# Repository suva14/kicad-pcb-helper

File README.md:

# kicad-pcb-helper

My notebook of lessons from designing KiCad boards with [Claude Code](https://claude.com/claude-code),
kept as a skill so the next project starts where the last one ended. It works alongside
[kicad-happy](https://github.com/aklofas/kicad-happy), which does the heavy design analysis; this
plugin adds what the hand rework of one real board taught: how a human places and routes, the check to
run after every save, the review before ordering, and JLCPCB placement files that land on the right pads.

## Origin

Everything started with **[kicad-happy](https://github.com/aklofas/kicad-happy)** by aklofas, a Claude
Code plugin that parses KiCad schematics and layouts, runs EMC pre-compliance, checks gerbers and
prepares boards for fabrication. It reviewed the design of a small battery-powered data logger
(ESP32-S3, 60 × 40 mm, 2 layers) that measures vibration on a bicycle for rolling-resistance studies.

On that project, Claude produced the first complete, DRC-clean board; I then reworked it by hand,
asking Claude to check after every save. The rework took the board from 166 vias to 98, brought
decoupling capacitors from 6 to 16 mm away down to about 2 mm, removed 50 useless ground tracks, and
exposed a JLC placement file that had silently rotated four ICs. This repository keeps those lessons and
the scripts written along the way, for my next boards and for anyone who finds them useful. The
measured comparison is in [`references/ai-vs-human.md`](skills/kicad-pcb-helper/references/ai-vs-human.md).

## What it does

- **Check after each save**: DRC with schematic parity on a complete copy of the project, what moved,
  per-net length and via changes, ground pour pieces and islands, decoupling distances, vias in pads.
- **Human layout methods from the start**: regulator beside its load, capacitor on its pin, pull-ups at
  the connector, parts in pin order, no ground exit tracks, stitching only where it matters.
- **"Will it work?" review**: pinout of every active part against the part actually bought, the role
  and side of every resistor, what is missing, the obligations the schematic puts on the firmware.
- **JLCPCB CPL fitted on JLC's footprints**: each part's EasyEDA footprint is downloaded and laid on
  the board's pads, pin by pin, to find the true position and rotation. A checker audits any CPL.

## Install

In Claude Code:

```
/plugin marketplace add suva14/kicad-pcb-helper
/plugin install kicad-pcb-helper@kicad-pcb-helper
```

The skill loads itself when you work on a KiCad board ("check my board", "recheck", "prepare the JLC
files", "the part is offset in the Component Placements preview"...).

## Examples

Real outputs from the project above, shortened; the first one combines two successive checks.

**"I rerouted and moved a few parts, check."** The human saves; the skill reads the save time, runs
the check, and reports only what matters:

```
saved 2026-10-16 17:15:06
DRC {('warning', 'silk_edge_clearance'): 2, ...} | unconnected 0 | parity 0
now: vias 98 (/GND 29) | tracks 1288 mm | near-zero segments 1 | /GND pour pieces (mm2) {'F.Cu': [1588, 28], 'B.Cu': [1856]}
  near-zero segment /EN B.Cu (110.24; 110.26)
  moved TP6   (114.00; 113.00 r0) -> (123.00; 106.00 r0)  flipped
  /TXD0          18.9 -> 7.0 mm, vias 1 -> 1
  C15  100nF    1.8 mm from U5-2 (/+3V3) | shared ground yes | nearest ground via 3.0 mm
```

**"The ESP32 is offset in JLC's Component Placements preview."** The placement file had been made with
a community rotation table. `jlc_cpl.py --check` lays JLC's own footprint of each part on the board:

```
J1    C165948    shift 6.52 mm, spread 3.50 mm WRONG  -> should be 154.229 -113.500 rot 90
U1    C7519      shift 0.00 mm, spread 2.11 mm WRONG  -> should be 152.800 -121.600 rot 270
U5    C2913202   shift 3.63 mm, spread 0.02 mm WRONG  -> should be 121.000 -110.377 rot 0
...
11 part(s) misplaced
```

A USB-C connector facing inwards, ESD arrays, the regulator and the RTC turned by 90 degrees, the module
3.6 mm off: all fixed before the order, by regenerating the file with `jlc_cpl.py`.

**"Which ground tracks can I delete?"** On the AI-routed board:

```
/GND vias 77 | exits 55 | redundant (pad already in the main pour) 50
   C10-2    exit via at (118.50; 131.59), next /GND via 2.5 mm from the pad
   ...
```

## Limitations

- Two-layer boards are what it was built and tested on. Four-layer boards work for the checks, but the
  ground-pour logic only looks at the outer layers.
- The CPL fit needs the LCSC part number of each part and the EasyEDA footprint behind it; parts with
  no common pin numbers between the two footprints are reported, not fitted. Top side only.
- EasyEDA's API is unofficial and rate-limited; the scripts cache what they download.
- The review checklist guides Claude; it does not replace reading the datasheets of the parts you buy.
- It never orders, pays, or submits anything: the human stays in charge of the manufacturer's site.

## Requirements

- KiCad 8 or later (developed on KiCad 10, Windows). The scripts run with **KiCad's own Python**,
  which provides the `pcbnew` module, and call `kicad-cli` (found next to that Python, on the PATH, or
  through `KICAD_CLI`).
- `curl` on the PATH for the JLC placement scripts (downloads EasyEDA footprints).
- Recommended: [kicad-happy](https://github.com/aklofas/kicad-happy), for schematic and layout analysis,
  EMC scoring and gerber checks. This plugin complements it and does not replace it.

## Scripts

Run them yourself too: on Windows, `"C:/Program Files/KiCad/10.0/bin/python.exe" script.py ...`.

| Script | Purpose |
|---|---|
| `board_check.py board.kicad_pcb` | full check, compared with the previous run |
| `jlc_cpl.py board.kicad_pcb --bom BOM.csv -o CPL.csv` | JLCPCB placement file fitted on JLC's footprints |
| `jlc_cpl.py board.kicad_pcb --bom BOM.csv --check CPL.csv` | audit an existing placement file |
| `pin_check.py board.kicad_pcb --bom BOM.csv` | each pad's net beside the pin name of the part actually bought |
| `gnd_via_spots.py board.kicad_pcb --net SPI_SCK` | free spots for a ground via next to a signal's vias |
| `redundant_gnd_exits.py board.kicad_pcb` | ground exit tracks a solid pour makes useless |

All scripts only read the board. They live in `skills/kicad-pcb-helper/scripts/`.

Each script also has its own command in Claude Code, which runs it and reads the result:

| Command | Runs |
|---|---|
| `/kicad-pcb-helper:board-check` | `board_check.py` |
| `/kicad-pcb-helper:pin-check` | `pin_check.py` |
| `/kicad-pcb-helper:jlc-cpl` | `jlc_cpl.py` |
| `/kicad-pcb-helper:gnd-via-spots` | `gnd_via_spots.py` |
| `/kicad-pcb-helper:redundant-gnd-exits` | `redundant_gnd_exits.py` |

`/kicad-pcb-helper:kicad-pcb-helper` loads the whole method (rules, review, JLC).

## Tests

`tests/fixture/demo.kicad_pcb` is a 30 × 20 mm board built by `tests/make_fixture.py` with one planted
defect per check (a far decoupling capacitor, a via in a pad, a redundant ground exit, a signal via
without stitching, a SOT-23-5 that a fixed rotation table gets wrong). Run:

```
"C:/Program Files/KiCad/10.0/bin/python.exe" tests/run_tests.py
```

The JLC test downloads one EasyEDA footprint and is skipped offline.

## Layout

```
.claude-plugin/          plugin and marketplace manifests
skills/kicad-pcb-helper/
  SKILL.md               the method: ground rules, check loop, placement, routing, review, JLC
  references/            the measured AI-versus-human rework, JLC placement details
  scripts/               the checks
tests/                   demo board with planted defects, and the test runner
```

## License

MIT: use it, fork it, adapt it to your own boards; keep the copyright notice.

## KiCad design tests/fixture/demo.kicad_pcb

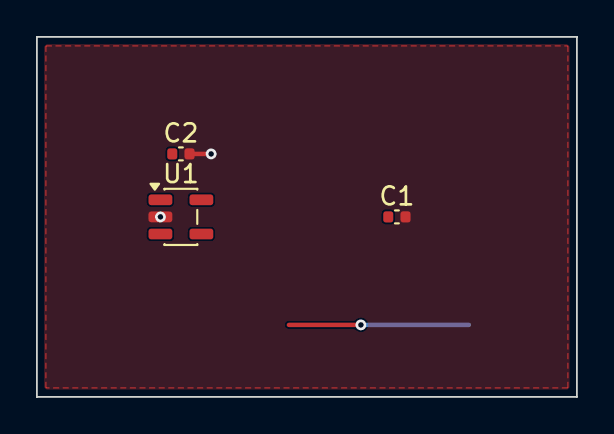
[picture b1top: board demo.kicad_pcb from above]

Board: 2 copper layers, 30.0 x 20.0 mm, 3 parts (0 on the bottom side), 2 nets.

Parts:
C1, C2: C_0402_1005Metric
U1: SOT-23-5

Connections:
GND: C1.2, C2.2, U1.2
VCC: C1.1, C2.1, U1.1
